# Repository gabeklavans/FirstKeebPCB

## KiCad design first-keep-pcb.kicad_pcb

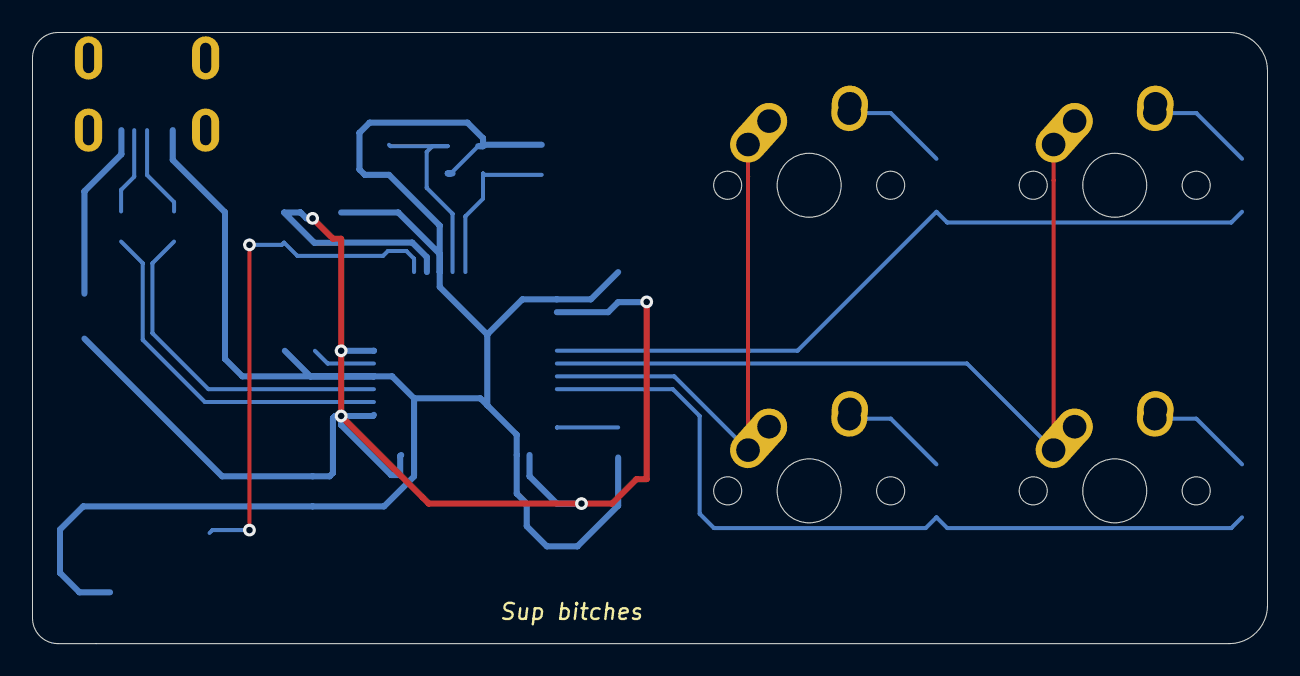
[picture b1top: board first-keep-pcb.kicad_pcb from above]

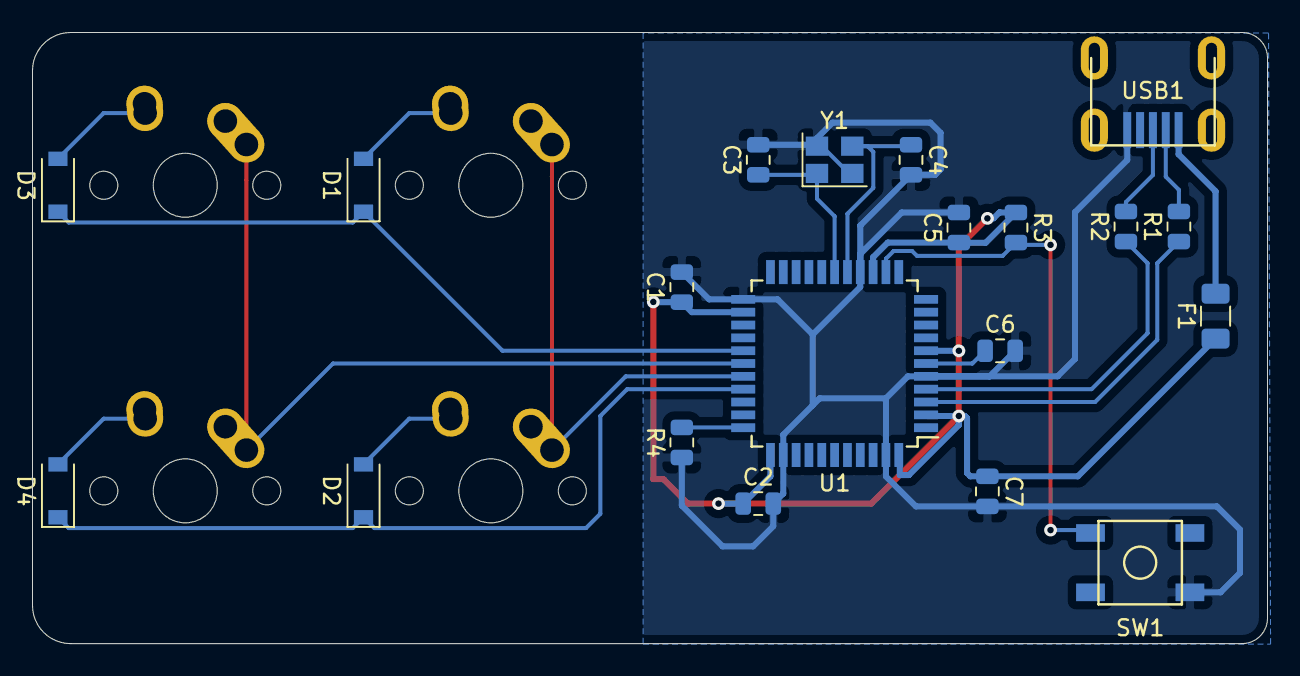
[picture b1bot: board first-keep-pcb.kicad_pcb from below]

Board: 2 copper layers, 77.0 x 38.1 mm, 24 parts (20 on the bottom side), 20 nets.

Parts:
C1, C2, C5: 0.1uF; C_0805_2012Metric
C3, C4: 22pF; C_0805_2012Metric
C6: 1uF; C_0805_2012Metric
C7: 10uF; C_0805_2012Metric
D1, D2, D3, D4: SOD-123; D_SOD-123
F1: 500mA; Fuse_1206_3216Metric
MX1, MX2, MX3, MX4: MX-NoLED; MX-1U-NoLED
R1, R2: 22; R_0805_2012Metric
R3, R4: 10k; R_0805_2012Metric
SW1: SW_Push; SKQG-1155865
U1: ATmega32U4-AU; TQFP-44_10x10mm_P0.8mm
USB1: Molex-0548190589
Y1: 16MHz; Crystal_SMD_3225-4Pin_3.2x2.5mm

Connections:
+5V: C1.1, C2.1, C5.1, C7.1, F1.1, R3.1, U1.2, U1.7, U1.14, U1.24, U1.34, U1.44
COL0: MX1.1, MX2.1, U1.29
COL1: MX3.1, MX4.1, U1.28
D+: R2.2, USB1.3
D-: R1.2, USB1.4
GND: C1.2, C2.2, C3.2, C4.2, C5.2, C6.2, C7.2, R4.1, SW1.1, U1.5, U1.15, U1.23, U1.35, U1.43, USB1.1, Y1.2, Y1.4
unnamed: C3.1, U1.17, Y1.1
unnamed: C4.1, U1.16, Y1.3
unnamed: C6.1, U1.6
unnamed: D1.2, MX1.2
unnamed: D2.2, MX2.2
unnamed: D3.2, MX3.2
unnamed: D4.2, MX4.2
unnamed: R1.1, U1.3
unnamed: R2.1, U1.4
unnamed: R3.2, SW1.2, U1.13
unnamed: R4.2, U1.33
ROW0: D1.1, D3.1, U1.27
ROW1: D2.1, D4.1, U1.30
VCC: F1.2, USB1.5

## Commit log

2020-06-20 Added kicad proj files
2020-06-20 added submodules for footprint libs
2020-06-20 added footprint libs
2020-06-20 Added comps to schematic
2020-06-20 Added components to schematic
2020-06-20 Placed all pcb components
2020-06-21 Added routing
2020-06-21 Added custom flair
2020-06-21 Completed design and generated gerber files
2020-06-21 Probably nothing
